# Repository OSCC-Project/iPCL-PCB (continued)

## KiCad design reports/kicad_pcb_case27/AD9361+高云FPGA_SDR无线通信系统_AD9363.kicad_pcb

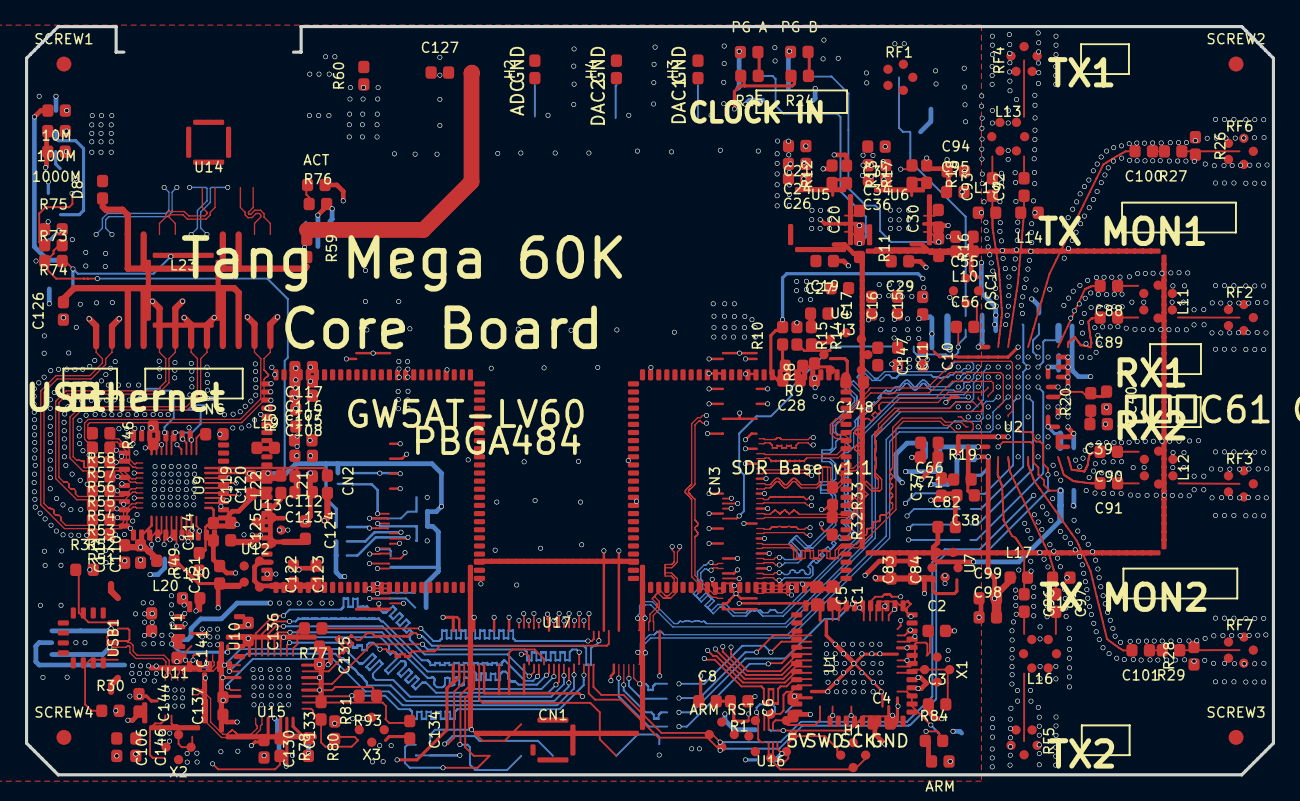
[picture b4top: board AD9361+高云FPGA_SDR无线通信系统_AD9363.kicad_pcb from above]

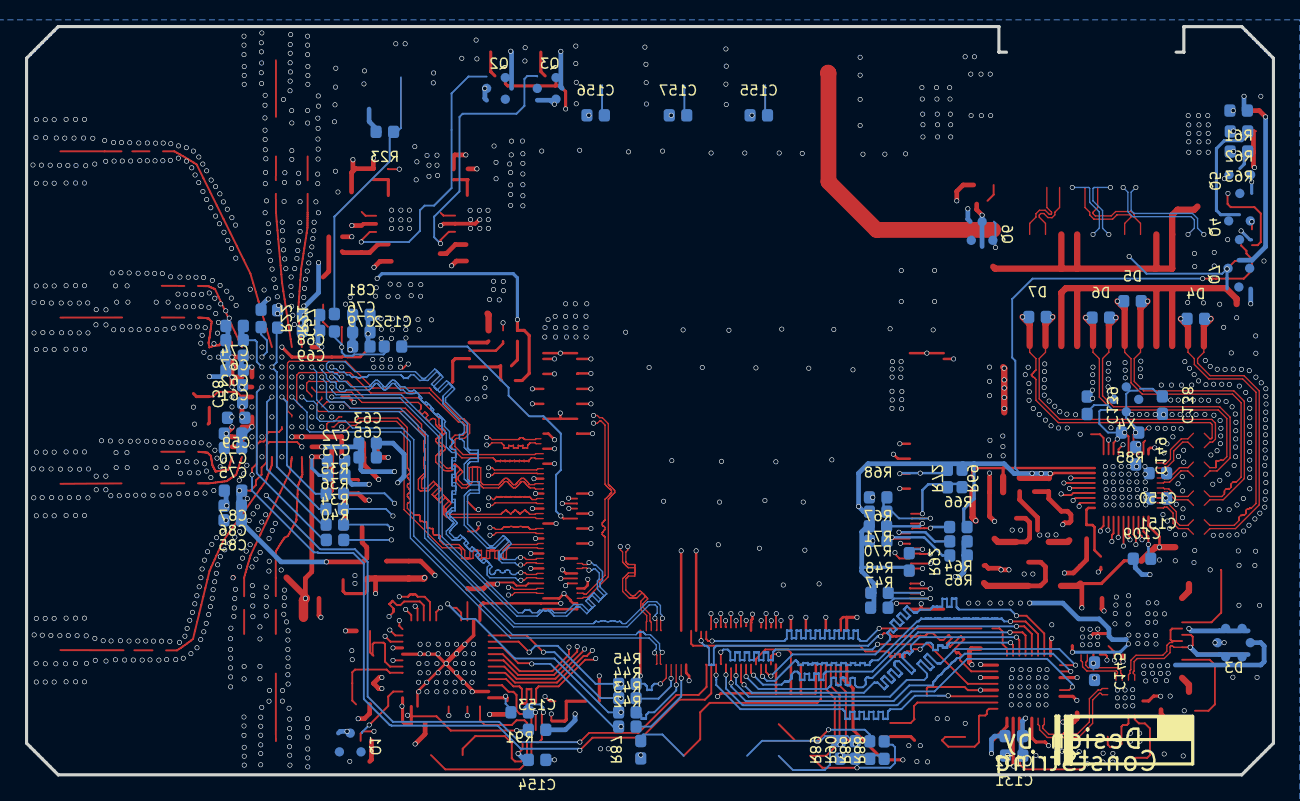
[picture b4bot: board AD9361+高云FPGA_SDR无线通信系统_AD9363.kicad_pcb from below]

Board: 4 copper layers, 100.0 x 60.0 mm, 274 parts (82 on the bottom side), 245 nets.

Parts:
10M, 100M, 1000M: 81ffb88415c44813ae88209955e7c78c
ACT: 81ffb88415c44813ae88209955e7c78c
ARM: 81ffb88415c44813ae88209955e7c78c
ARM RST: 7dd6720d68c446719365f3a60b06a3d4
C1, C2, C3, C4, C5, C6, C8, C20, C24, C26, C27, C28, C30, C34, C36, C37, C38, C39, C40, C55, C56, C57, C58, C59, C61, C62, C63, C65, C66, C67, C68, C69, C70, C71, C72, C73, C74, C75, C76, C79, C85, C86, C87, C88, C89, C90, C91, C92, C93, C95, C96, C97, C99, C100, C101, C107, C108, C109, C110, C111, C112, C113, C114, C115, C116, C117, C119, C120, C126, C130, C131, C133, C134, C135, C136, C137, C138, C139, C140, C141, C144, C145, C146, C147, C148, C149, C150, C151, C152, C153, C154, C155, C156, C157: 2218026411c24ad7aa8c7eefc9fb0747
C10, C11, C15, C16, C17: bd62313503d94485b107ad99fc121a58
C19, C21, C29, C31, C81, C82, C83, C84, C94, C98, C106, C121, C122, C123, C124, C125, C132: b6dbb5ff8ac44442903843d0a49ba1b4
C127: 1f480a04812e476d85878241a76d6dab
CN1: 7fd91c8eb86f4ef493fcae420cc5a236
CN2, CN3: b10a9c17a09f40588c51376b90a8528a
D3: 31aeffc65a7040bea0c61d6139a11c18
D4, D5, D6, D7: b31a530e17ae47c5b04672837fb6799c
D8: c10007abe38c47a7b87ab16ff611ce54
F1: e1e246e4058e4f2cb0164869e14091ad
H1: 507350d26ffb4301b926e73910155355
H2, H3, H4: 2a4ef173d7bb4178ba727836363a3722
L10, L20, L21, L22: 8e29569e39fd44aa8c43aaaf80cd9083
L11, L12, L13, L16: 63f67b374b2243b18a84cd74cbe2f3f3
L14, L15, L17, L18: 179f3791b8784cc680c437a3efdd4b04
L19: cbf6cd5da4ff4b4385b17ae7bcff98d5
L23: d78d442e09c0422188aa45615f3a3d0e
NC: 073582d7bdef4f49a1284c73eea18806
OSC1: 6182a2c878e549158f1d9c038c5ce7a3
PG A: 30f1d73fe7104a6986f78cf331c4975f
PG B: 30f1d73fe7104a6986f78cf331c4975f
Q1, Q2, Q3, Q4, Q5, Q6: f9aee2f635684ce29874ae31607c59e5
Q7: f5cc4a0a92d24ce5a40aa6a7c1fedc9f
R1, R8, R9, R10, R11, R12, R13, R14, R15, R16, R17, R18, R19, R20, R21, R22, R23, R24, R25, R26, R27, R28, R29, R30, R31, R32, R33, R34, R35, R36, R40, R42, R43, R44, R45, R46, R47, R48, R49, R50, R51, R52, R53, R54, R55, R56, R57, R58, R61, R62, R63, R64, R65, R66, R67, R68, R69, R70, R71, R72, R73, R74, R75, R76, R77, R78, R80, R81, R84, R85, R86, R87, R88, R89, R90, R91, R92, R93: 073582d7bdef4f49a1284c73eea18806
R59, R60: 98cf0348c8144cb19a93da813708cb62
RF1: aa04b55d95ab4d16b10c242528f5914c
RF2, RF3, RF4, RF5, RF6, RF7: f7525c14c0624ba49d44b90f489655c1
SCREW1: e584
SCREW2: e585
SCREW3: e587
SCREW4: e589
U1: d4d1bbb6b3024aa89e210277779a1524
U2: 44c17d15bf524a95900276da06795e90
U3: c65eff752ba2425191bd24655060057f
U4: b9df9a449868427a838a73cc143e1fe6
U5, U6: 34d530a420af4d6fbf68b1a8a67ad2c2
U7, U12, U13: fc24ab5a59e648c2b5c9dd79cfa5a276
U9: 6a1d45914ae84bee8d2c010ea94bd60d
U10: 1c7bc24088074f01866a2314a22fcef9
U11: 87c69e2cf3154d7c86d08ffd1fcbba79
U14: b9780a7aece7405fba878a3714394c2b
U15: 3f32b4c241834b3ba524ce5ae7f08632
U16: 68d9d0e5ebdd4a91b9118051fb54c8c4
U17: 091dc6707f3c4b86bc4edc7ea8aebfad
USB1: 090befb01a1c47f086e739b53b55ac0a
X1, X2, X3, X4: baa95a22880b4a62b1cd14ca4a928589

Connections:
1V3_A: C21.2, C24.2, C26.2, C58.2, C59.2, C61.2, C62.2, C63.2, C65.2, R12.2, U2.B9, U2.B10, U2.E2, U2.F2, U2.J3, U2.K3, U5.10, U5.11, U5.12, U5.13, U5.14
1V3_B: C31.2, C34.2, C36.2, C66.2, C67.2, C68.2, C69.2, C70.2, C71.2, C72.2, C73.2, C74.2, C75.2, C94.2, C95.2, C98.2, C99.2, L14.1, L15.1, L17.1, L18.1, R17.2, U2.A9, U2.A10, U2.D2, U2.D3, U2.E3, U2.F12, U2.K4, U2.M9, U2.M10, U6.10, U6.11, U6.12, U6.13, U6.14
1V8: C4.2, C5.2, C6.2, C15.2, C16.2, C17.2, C19.2, C28.2, C29.2, C76.2, C79.2, C81.2, C153.2, CN2.50, CN3.50, L10.2, R1.1, R10.2, R11.2, R16.2, R21.2, R91.1, U1.1, U1.9, U1.24, U1.36, U1.48, U2.H12, U4.2, U5.1, U5.2, U5.3, U5.4, U5.15, U5.16, U6.1, U6.2, U6.3, U6.4, U6.15, U6.16, U16.1, U17.26
3V3: C82.1, C85.2, C86.2, C87.2, C154.1, R86.2, R87.2, R88.2, R89.2, R90.2, U2.B8, U7.5, U16.8
5V: 100M.2, 1000M.2, ACT.2, C10.2, C11.2, C83.1, C84.2, C122.1, C123.2, C124.2, C141.1, C144.1, C147.2, CN2.1, CN2.2, CN2.3, CN2.4, CN2.5, CN2.6, F1.2, H1.1, Q7.2, R15.1, R24.2, R25.2, R78.2, R84.2, U3.2, U7.1, U7.3, U10.3, U10.9, U11.15, U12.1, U12.3, U13.1, U13.3
$2N1720: C37.2, R19.1
$2N3444: C39.2, R20.1
$2N3451: C40.1, R20.2, U2.G2, U2.G3
$2N3895: R22.1, U2.L4
$2N4930: C55.1, L10.1, OSC1.4
$2N4992: C56.2, OSC1.3
$2N5256: C57.1, R23.2, RF1.5
$3N848: R15.2, U3.6
$3N852: C27.2, U3.3, U4.1
$3N853: C27.1, R14.1
$3N854: R14.2, U3.5
$3N857: C28.1, R8.2, R9.1, U3.8
$3N1060: R9.2, R10.1
$3N1717: C20.2, U5.7
$3N1832: R12.1, R13.2, U5.9
$3N3032: C30.2, U6.7
$3N3034: R17.1, R18.2, U6.9
$3N6807: PG B.2, R24.1
$3N6848: PG A.2, R25.1
$3N15876: C148.2, U3.7
$3N21957: PG B.1, Q2.3
$3N22008: PG A.1, Q3.3
$4N680: C1.2, U1.22
$4N3637: ARM.2, R84.1
$4N6007: ARM.1, Q1.3
$4N6427: R91.2, U16.5
$5N375: R31.1, USB1.4
$5N379: R30.1, USB1.10
$5N1334: C145.2, U10.6
$5N1646: U11.2, X2.1
$5N1650: U11.1, X2.3
$5N1903: C106.1, C146.1, U11.16
$6N381: L11.3, RF2.5
$6N492: C88.1, L11.6
$6N497: C89.1, L11.4
$6N753: L12.3, RF3.5
$6N755: C90.1, L12.6
$6N758: C91.1, L12.4
$6N915: L13.3, RF4.5
$6N1077: C92.2, L13.4
$6N1083: C93.2, L13.6
$6N1770: C97.2, L16.6
$6N1788: C96.2, L16.4
$6N1797: L16.3, RF5.5
$6N2135: R26.2, R27.1, RF6.5
$6N2141: C100.1, R27.2
$6N2367: C101.1, R29.2
$6N2369: R28.2, R29.1, RF7.5
$7N989: L19.1, U9.30
$7N1109: NC.1, U9.31
$7N1265: R46.1, U9.39
$7N3719: D4.1, L23.1, R51.2
$7N3729: D4.2, L23.2, R52.2
$7N3751: D5.1, L23.5, R53.2
$7N3757: D5.2, L23.6, R54.2
$7N3761: D6.1, L23.7, R55.2
$7N3767: D6.2, L23.8, R56.2
$7N3774: D7.1, L23.11, R57.2
$7N3784: D7.2, L23.12, R58.2
$7N4429: C126.2, L23.3, L23.4, L23.9, L23.10
$7N4503: D8.1, L23.15, L23.16, L23.21, L23.22, R59.2
$7N4793: C127.2, R59.1
$7N8958: 10M.1, R61.1
$7N8975: 100M.1, R62.1
$7N8992: 1000M.1, R63.1
$7N9856: ACT.1, R76.1
$7N51860: Q4.3, R62.2
$7N51864: Q5.3, R63.2
$7N51869: Q6.3, R76.2
$7N52042: 10M.2, Q7.3
$8N749: R77.2, U15.1
$8N854: C130.1, U15.20, U15.23
$8N1159: R78.1, U15.22
$8N1371: R80.1, U15.24
$8N1466: C134.1, R81.1, U15.26, X3.1
$8N1479: C133.1, R81.2, U15.25, X3.3
ARM_COM_D0: U1.10, U17.62
ARM_COM_D1: U1.11, U17.61
ARM_COM_D2: U1.12, U17.60
ARM_COM_D3: U1.13, U17.57
ARM_COM_D4: U1.14, U17.56
ARM_COM_D5: U1.15, U17.55
ARM_COM_D6: U1.16, U17.54
ARM_COM_D7: U1.17, U17.53
ARM_COM_S0: U1.29, U17.63
ARM_COM_S1: U1.30, U17.64
ARM_COM_S2: U1.31, U17.65
ARM_COM_S3: U1.32, U17.66
ARM_COM_S4: U1.33, U17.67
ARM_LED: Q1.1, U1.2
ARM_NRST: ARM RST.2, C8.2, R1.2, U1.7
ARM_OSC_IN: C3.2, U1.5, X1.3
ARM_OSC_OUT: C2.1, U1.6, X1.1
ARM_SPI2_EN: R44.2, U1.26, U2.K6
ARM_SPI2_MISO: R45.2, U1.27, U2.L6
ARM_SPI2_MOSI: R42.2, U1.28, U2.J4
ARM_SPI2_SCK: R43.2, U1.21, U2.J5
ARM_SWCLK: U1.37, U16.2
ARM_SWCLK_3V3: H1.3, U16.6
ARM_SWDIO: U1.34, U16.3
ARM_SWDIO_3V3: H1.2, U16.7
ARM_UART_RX: U1.39, U10.4
ARM_UART_TX: U1.42, U10.5
AUX_ADC: C155.1, H2.1, U2.L5
AUX_DAC1: C156.1, H3.1, U2.B3
AUX_DAC2: C157.1, H4.1, U2.C3
BANK1_A13_IOT95A: CN3.26, U2.G9
BANK1_A14_IOT95B: CN3.27, R33.1, U2.H9
BANK1_A15_IOT99A: CN3.32, U2.F10
BANK1_A16_IOT99B: CN3.33, R32.1, U2.G10
BANK1_B13_IOT93B: CN3.24, U2.E9
BANK1_B15_IOT97A: CN3.29, U2.D10
BANK1_B16_IOT97B: CN3.30, U2.E11
BANK1_B17_IOT104A: CN3.38, U2.D11
BANK1_B18_IOT104B: CN3.39, U2.E12
BANK1_C13_IOT93A: CN3.23, U2.D8
BANK1_C14_IOT85A: CN3.20, U2.E7
BANK1_C15_IOT85B: CN3.21, U2.F8
BANK1_C17_IOT106B: CN3.36, U2.E10
BANK1_D14_IOT82A: C152.1, CN3.68
BANK1_D17_IOT106A: CN3.35, U2.D9
BANK1_E13_IOT78A: CN3.17, U2.D7
BANK1_E14_IOT78B: CN3.18, U2.E8
BANK1_F13_IOT80A: CN3.72, R35.1
BANK1_F14_IOT80B: CN3.71, R36.1
BANK1_F15: CN3.70, R34.1
BANK2_A18_IOT113A: CN3.41, U2.J12
BANK2_A19_IOT113B: CN3.42, U2.K11
BANK2_A20_IOT122B: CN3.45, U2.K10
BANK2_A21_IOT135B: CN3.48, U2.J7
BANK2_B20_IOT122A: CN3.44, U2.J11
BANK2_B21_IOT135A: CN3.47, U2.H8
BANK2_B22_IOT133B: U2.G7, U17.3
BANK2_C18_IOT115A: CN3.59, U2.G11
BANK2_C19_IOT115B: CN3.58, U2.H11
BANK2_C20_IOT131B: CN3.52, U2.K7
BANK2_C22_IOT133A: U2.G8, U17.4
BANK2_D19_IOT120B: CN3.55, R40.1
BANK2_D20_IOT131A: CN3.53, U2.J8
BANK2_D21_IOT138B: U2.J9, U17.80
BANK2_D22_IOT140B: U2.K9, U17.78
BANK2_E18_IOT117B: R45.1, U17.5
BANK2_E19_IOT120A: CN3.56, U2.J6
BANK2_E21_IOT138A: U2.K8, U17.79
BANK2_E22_IOT140A: U2.J10, U17.77
BANK2_F18_IOT117A: R44.1, U17.6
BANK2_G21_IOT144A: R42.1, U17.8
BANK2_G22_IOT144B: R43.1, U17.7
BANK5_H19_IOR41B: U15.31, U17.69
BANK5_H20_IOR43A: U15.2, U17.71
BANK5_H22_IOR45B: R93.2, U15.27, U17.15
BANK5_J19_IOR41A: R77.1, U17.68
BANK5_J20_IOR54A: U2.D6, U17.14
BANK5_J21_IOR54B: U2.E5, U17.13
BANK5_J22_IOR45A: U15.29, U17.16
BANK5_K21_IOR59A: U15.10, U17.18
BANK5_K22_IOR59B: U15.13, U17.17
BANK5_L19_IOR61A: U15.3, U17.20
BANK5_L20_IOR61B: U15.9, U17.19
BANK5_L21_IOR68B: U15.4, U17.21
BANK5_M21_IOR68A: U15.5, U17.22
BANK5_M22_IOR63B: U15.6, U17.24
BANK5_N22_IOR63A: U15.7, U17.25
BANK8_AA18_IOB77A: CN2.38, Q6.1
BANK8_AA19_IOB85A: CN2.42, U9.18
BANK8_AB18_IOB77B: C109.1, CN2.39, R92.2, U9.12
BANK8_AB20_IOB85B: CN2.43, U9.17
BANK8_AB21_IOB97A: CN2.46, U9.16
BANK8_AB22_IOB97B: CN2.47, U9.15
BANK8_U17_IOB75A: CN2.32, R69.1, R72.2, U9.25
BANK8_U18_IOB75B: CN2.33, R68.1, R71.2, U9.24
BANK8_V17_IOB79A: CN2.34, R67.1, R70.2, U9.23
BANK8_W17_IOB79B: CN2.35, R66.2, U9.22
BANK8_W19_IOB93A: CN2.40, U9.20
BANK8_W20_IOB93B: CN2.41, U9.19
BANK8_Y18_IOB87A: CN2.36, R64.1, U9.26
BANK8_Y19_IOB87B: CN2.37, R65.1, U9.27
BANK8_Y21_IOB99A: CN2.48, R48.1, U9.14
BANK8_Y22_IOB99B: CN2.49, R47.1, U9.13
BANK12_R13_JTAG_TDI: CN1.9, R87.1, U17.36
BANK12_T13_JTAG_TMS: CN1.5, R90.1, U17.39
BANK12_U13_JTAG_TDO: CN1.3, R89.1, U17.38
BANK12_V12_JTAG_TCK: CN1.1, R88.1, U17.37
DN: D3.1, D3.6, U11.11, USB1.5, USB1.7
DP: D3.3, D3.4, U11.12, USB1.6, USB1.8
ENABLE: R35.2, U2.G6
EN_AGC: R34.2, U2.G5
ETH0_MDI0_N: L23.14, U14.2
ETH0_MDI0_P: L23.13, U14.1
ETH0_MDI1_N: L23.18, U14.6
ETH0_MDI1_P: L23.17, U14.3
ETH0_MDI2_N: L23.20, U14.5
ETH0_MDI2_P: L23.19, U14.4
ETH0_MDI3_N: L23.24, U14.8
ETH0_MDI3_P: L23.23, U14.7
GND: ARM RST.3, C1.1, C2.2, C3.1, C4.1, C5.1, C6.1, C8.1, C10.1, C11.1, C15.1, C16.1, C17.1, C19.1, C20.1, C21.1, C24.1, C26.1, C29.1, C30.1, C31.1, C34.1, C36.1, C37.1, C38.2, C39.1, C40.2, C55.2, C58.1, C59.1, C61.1, C62.1, C63.1, C65.1, C66.1, C67.1, C68.1, C69.1, C70.1, C71.1, C72.1, C73.1, C74.1, C75.1, C76.1, C79.1, C81.1, C82.2, C83.2, C84.1, C85.1, C86.1, C87.1, C94.1, C95.1, C98.1, C99.1, C106.2, C107.2, C108.2, C109.2, C110.1, C111.1, C112.1, C113.1, C114.1, C115.1, C116.1, C117.1, C119.1, C120.1, C121.2, C122.2, C123.1, C124.1, C125.1, C126.1, C130.2, C131.1, C132.1, C133.2, C134.2, C135.1, C136.1, C137.1, C138.1, C139.2, C140.2, C141.2, C144.2, C145.1, C146.2, C147.1, C148.1, C149.1, C150.1, C151.1, C153.1, C154.2, C155.2, C156.2, C157.2, CN1.10, CN2.7, CN2.8, CN2.9, CN2.10, CN2.11, CN2.12, CN2.18, CN2.21, CN2.24, CN2.27, CN2.100, CN3.1, CN3.4, CN3.7, CN3.10, CN3.13, CN3.16, CN3.19, CN3.22, CN3.25, CN3.28, CN3.31, CN3.34, CN3.37, CN3.40, CN3.43, CN3.46, CN3.49, CN3.51, CN3.54, CN3.57, CN3.60, CN3.63, CN3.66, CN3.69, CN3.73, CN3.85, CN3.88, CN3.91, CN3.94, CN3.97, CN3.100, D3.2, H1.4, H2.2, H3.2, H4.2, L11.1, L11.2, L11.5, L12.1, L12.2, L12.5, L13.1, L13.2, L13.5, L16.1, L16.2, L16.5, NC.2, OSC1.2, Q1.2, Q2.2, Q3.2, Q4.2, Q5.2, Q6.2, R8.1, R13.1, R18.1, R22.2, R23.1, R26.1, R28.1, R30.2, R31.2, R32.2, R33.2, R46.2, R60.1, R61.2, R64.2, R65.2, R67.2, R68.2, R69.2, R75.2, R80.2, RF1.1, RF1.2, RF1.3, RF1.4, RF2.1, RF2.2, RF2.3, RF2.4, RF3.1, RF3.2, RF3.3, RF3.4, RF4.1, RF4.2, RF4.3, RF4.4, RF5.1, RF5.2, RF5.3, RF5.4, RF6.1, RF6.2, RF6.3, RF6.4, RF7.1, RF7.2, RF7.3, RF7.4, U1.8, U1.23, U1.35, U1.47, U1.49, U2.A4, U2.A6, U2.A12, U2.B1, U2.B2, U2.B12, U2.C1, U2.C2, U2.C4, U2.C7, U2.C8, U2.C9, U2.C10, U2.C11, U2.C12, U2.D1, U2.D12, U2.E1, U2.F1, U2.F3, U2.F7, U2.F9, U2.F11, U2.G1, U2.G12, U2.H1, U2.H2, U2.H3, U2.H5, U2.H6, U2.H7, U2.H10, U2.J1, U2.J2, U2.K1, U2.K2, U2.K12, U2.L1, U2.L2, U2.L3, U2.L7, U2.L8, U2.L9, U2.L10, U2.L11, U2.L12, U2.M4, U2.M6, U3.1, U3.4, U5.6, U5.17, U6.6, U6.17, U7.2, U9.41, U10.2, U10.17, U11.17, U12.2, U13.2, U15.33, U16.4, U17.9, U17.23, U17.27, U17.30, U17.32, U17.35, U17.40, U17.41, U17.44, U17.48, U17.51, U17.59, U17.70, U17.73, USB1.1, USB1.12, USB1.13, USB1.14, X1.2, X1.4, X2.2, X2.4, X3.2, X3.4, X4.2, X4.4
GNDS: C127.1, D8.2, R60.2, U14.9, U14.10
JTAG_VREF: CN1.4, R86.1
PG_1V3_A: Q3.1, R11.1, U5.5
PG_1V3_B: Q2.1, R16.1, U6.5
PHY0_1V8: C125.2, C135.2, C136.2, C137.2, C140.1, L22.1, R93.1, U10.1, U13.5, U15.8, U15.11, U15.14, U15.28, U15.30, U15.32
PHY0_3V3: C121.1, C131.2, C132.2, L20.1, L21.1, U12.5, U15.21
PHY0_AVDD_1V0: C115.2, C116.2, C117.2, C149.2, C150.2, C151.2, R50.2, U9.3, U9.8, U9.38
PHY0_AVDD_3V3: C110.2, C111.2, L20.2, U9.11, U9.40
PHY0_DVDD_1V0: C114.2, R49.2, U9.21
PHY0_DVDD_3V3: C112.2, C113.2, L21.2, U9.29
PHY0_LED0/CFG_EXT: Q7.1, R73.2, U9.32
PHY0_LED1/CFG_LDO0: Q4.1, R75.1, U9.33
PHY0_LED2/CFG_LDO1: Q5.1, R74.2, U9.34
PHY0_MDI0_N: R57.1, U9.2
PHY0_MDI0_P: R58.1, U9.1
PHY0_MDI1_N: R55.1, U9.5
PHY0_MDI1_P: R56.1, U9.4
PHY0_MDI2_N: R53.1, U9.7
PHY0_MDI2_P: R54.1, U9.6
PHY0_MDI3_N: R51.1, U9.10
PHY0_MDI3_P: R52.1, U9.9
PHY0_REG_1V0: C107.1, C108.1, L19.2, R49.1, R50.1
PHY0_VIO: C119.2, C120.2, L22.2, R47.2, R48.2, R66.1, R70.1, R71.1, R72.1, R73.1, R74.1, R92.1, U9.28
PHY0_XTAL_IN: C139.1, R85.1, U9.36, X4.1
PHY0_XTAL_OUT: C138.2, R85.2, U9.37, X4.3
RESETB: R21.1, R36.2, U2.K5
RX1A_N: C88.2, U2.M2
RX1A_P: C89.2, U2.M1
RX2A_N: C90.2, U2.A1
RX2A_P: C91.2, U2.A2
TX1A_N: C93.1, L15.2, U2.M8
TX1A_P: C92.1, L14.2, U2.M7
TX2A_N: C97.1, L18.2, U2.A7
TX2A_P: C96.1, L17.2, U2.A8
TXNRX: R40.2, U2.H4
TX_MON1: C100.2, U2.M5
TX_MON2: C101.2, U2.A5
TX_VCO_1V1: C38.1, R19.2, U2.A11, U2.B11
USART_DN: U10.8, U11.9
USART_DP: U10.7, U11.10
USB_DN: U11.7, U15.19
USB_DP: U11.8, U15.18
VBUS: D3.5, F1.1, USB1.2, USB1.11
XTALN: C56.1, C57.2, C152.2, U2.M12

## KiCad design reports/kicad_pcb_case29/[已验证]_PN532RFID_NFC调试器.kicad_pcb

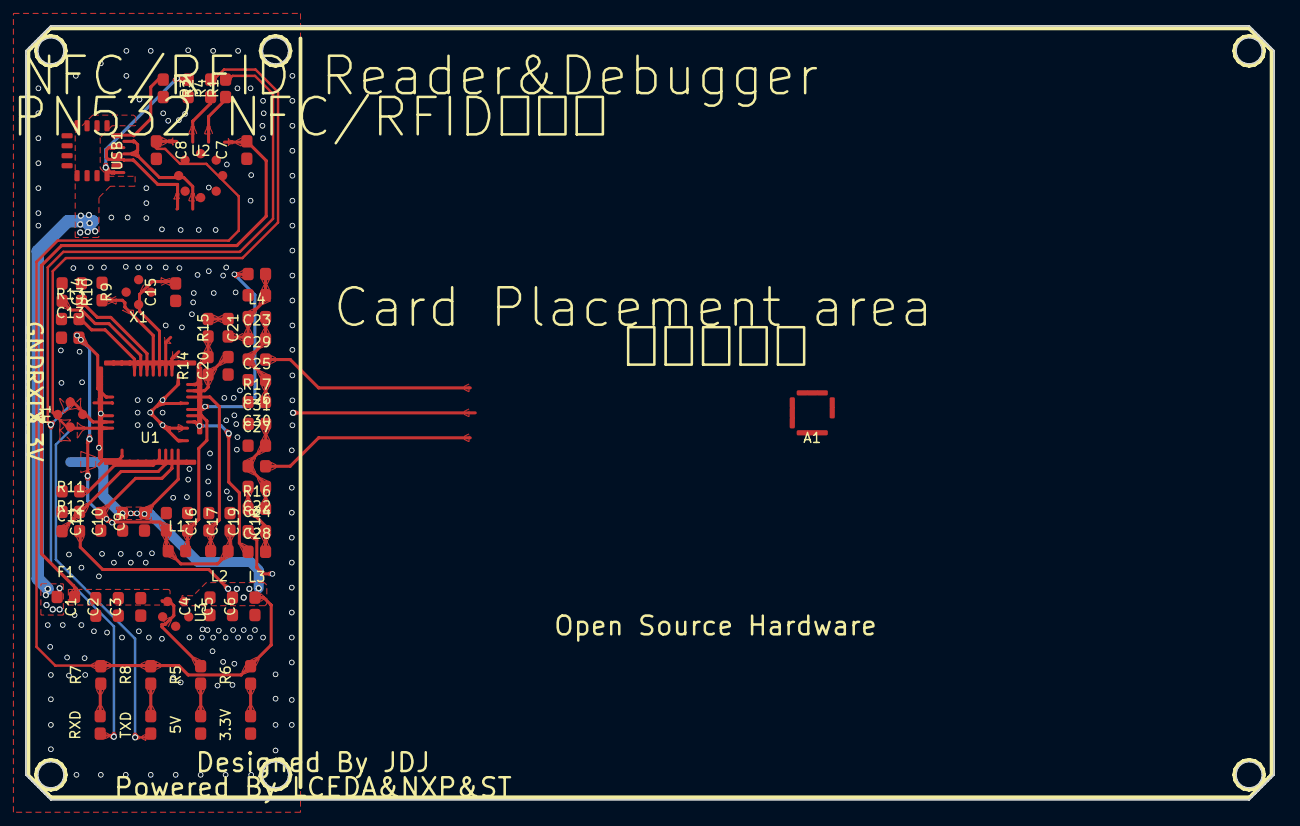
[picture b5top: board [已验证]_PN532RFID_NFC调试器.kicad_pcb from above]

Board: 4 copper layers, 100.0 x 62.0 mm, 64 parts (0 on the bottom side), 37 nets.

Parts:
3.3V: e18
5V: e17
A1: 7a9f0954cb3d4d10918b51f45fdb83fd
C1, C2, C3, C4, C5, C6, C7, C8, C9, C10, C11, C12, C13, C14, C15, C16, C17, C18, C19, C20, C21, C22, C23, C24, C25, C26, C27, C28, C29, C30, C31: 8f7a3719ddcd4fd8b3f45622f7cba8cd
F1: f3e1269709494694a1d8bce25b8ee1e8
H1: 03f4122eac2b40b49db6fc08b820e069
L1, L2, L3, L4: 720e450fbc4b486db1884a2c420b49c0
R1, R2, R5, R6, R7, R8, R9, R10, R11, R12, R14, R15, R16, R17: 0198c72b9ff6426ea0ee71ada792c43b
R3, R4, R13: 1064866dc1bf4bbd83bcacf9a79b5dbc
RXD: e19
TXD: e20
U1: 15638c3e09104a739cadb23dd1c3f9aa
U2: b1a0bcdb47574bcab0503576b89ba266
U3: 60e3120b69094052863bedef18c525dc
USB1: c94ffee73b93482cada48766b6ee1610
X1: 0f1cdad729404e7a8c291a360b05ecb5

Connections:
3.3V: C4.2, C5.2, C6.2, C8.1, C9.2, C10.2, H1.1, R6.2, R7.2, R8.2, R12.2, U1.40, U2.8, U3.5
5V: C1.2, C2.2, C3.2, C7.2, F1.2, R5.2, U2.5, U3.1, U3.3
532_RXD: H1.3, R4.2, RXD.1, U1.27
532_TXD: H1.2, R3.2, TXD.1, U1.28
$1N415: R1.1, USB1.B5
$1N465: R2.1, USB1.A5
$1N1931: R7.1, RXD.2
$1N1933: R8.1, TXD.2
$1N1935: 3.3V.2, R6.1
$1N1938: 5V.2, R5.1
$1N2593: C11.1, U1.37
$1N2815: R13.2, U1.18
$1N3520: C21.1, R15.2
$1N3576: L4.2, U1.6
$1N3579: L3.2, U1.4
$1N3784: C22.2, C24.2, C28.2, L3.1
$1N4004: C24.1, C26.2, C28.1, C30.2, R16.2
$1N4012: C25.1, C27.1, C29.1, C31.1, R17.2
ANT_TX1: A1.1, R16.1
ANT_TX2: A1.3, R17.1
AVDD: C19.2, L2.2, U1.8
CH340_RXD: R3.1, U2.7
CH340_TXD: R4.1, U2.6
GND: 3.3V.1, 5V.1, A1.2, C1.1, C2.1, C3.1, C4.1, C5.1, C6.1, C7.1, C8.2, C9.1, C10.1, C11.2, C12.1, C13.1, C14.2, C15.1, C16.1, C17.1, C18.1, C19.1, C20.1, C22.1, C23.2, C26.1, C27.2, C30.1, C31.2, H1.4, R1.2, R2.2, R9.1, R10.1, R11.1, R13.1, U1.1, U1.3, U1.7, U1.11, U1.41, U2.3, U3.2, USB1.13, USB1.14, USB1.15, USB1.16, USB1.A1B12, USB1.B1A12, X1.2, X1.4
OSCIN: C15.2, U1.14, X1.1
OSCOUT: C14.1, U1.15, X1.3
RES&OFF: R11.2, R12.1, U1.38
RX: C21.2, R14.2, U1.10
RXIN: C23.1, C25.2, C29.2, L4.1, R15.1
SET0: R9.2, U1.16
SET1: R10.2, U1.17
TVDD: C17.2, L1.2, U1.5
USB_N: U2.2, USB1.A7, USB1.B7
USB_P: U2.1, USB1.A6, USB1.B6
VBUS: F1.1, USB1.A4B9, USB1.B4A9
VMID: C20.2, R14.1, U1.9
VREF: C12.2, C13.2, C16.2, C18.2, L1.1, L2.1, U1.23, U1.39

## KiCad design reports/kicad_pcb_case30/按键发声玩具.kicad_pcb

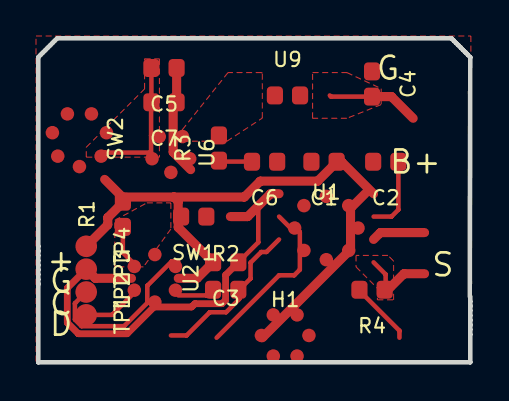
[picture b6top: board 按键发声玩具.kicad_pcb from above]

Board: 4 copper layers, 24.0 x 18.0 mm, 22 parts (0 on the bottom side), 15 nets.

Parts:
C1, C2, C3, C4, C5, C6, C7: bb17d5219181498b9e1395dbbf8b2fe0
H1: 36dfb2ea8d0e4e4f941cdac11c2fdbcb
R1, R2, R3, R4: 6658a532062f413bbac78fd6cbacbec5
SW1: 0139965c3fc24029a6435b55c53d32a5
SW2: 4f7abb5580174329a4a8b603a65d0e32
TP1, TP2, TP3, TP4: 59b65f4f99964ad8baf1fa180364e617
U1: 18bc969258c74e7298cb5068ceb95bdf
U2: 1f7687c352a74bcf9a3411407622aafa
U6: df62239e231b484093deec575f9a38e3
U9: e988ea007c7f4b938b03e561bd5e10d0

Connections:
$1N3367: R2.1, U2.4
$1N6451: C6.2, R3.1
$1N6655: H1.6, R4.2
BAT+: C4.2, U9.2
CLK: TP2.1, U2.6
DAT: TP1.1, U2.3
DATA/TX: H1.1, R2.2, U1.3
GND: C1.2, C2.2, C3.1, C4.1, C5.1, C6.1, C7.1, H1.4, H1.5, SW1.1, TP3.1, U1.1, U2.2, U6.4
RX: H1.2, U1.2
SPK1: R4.1, U1.5
SW: R3.2, U6.5, U9.1
SW1: R1.1, SW1.2, U2.1
VCC: C1.1, C3.2, H1.3, R1.2, SW2.3, TP4.1, U1.8, U2.5
VOUT: C5.2, C7.2, SW2.2, U6.1, U6.2
VREF: C2.1, U1.7

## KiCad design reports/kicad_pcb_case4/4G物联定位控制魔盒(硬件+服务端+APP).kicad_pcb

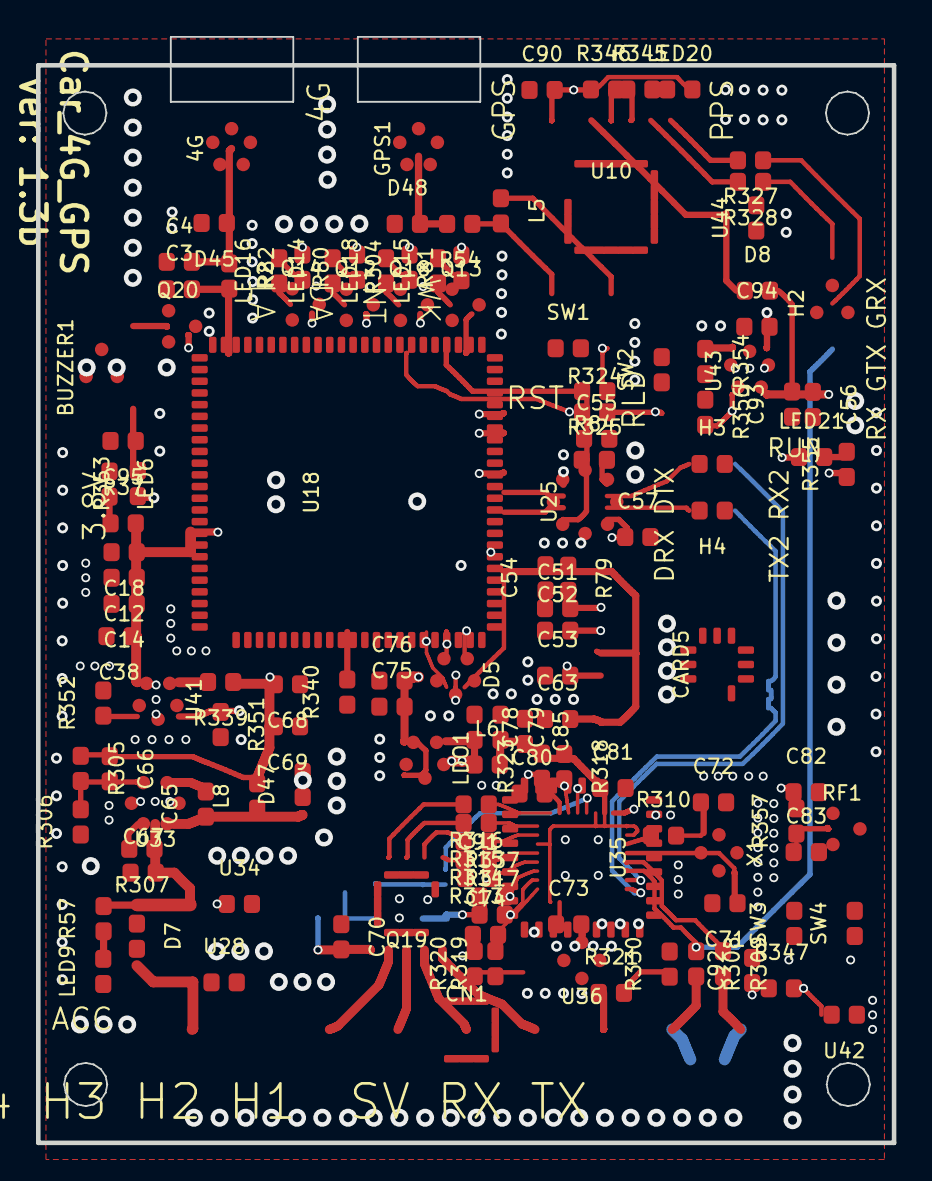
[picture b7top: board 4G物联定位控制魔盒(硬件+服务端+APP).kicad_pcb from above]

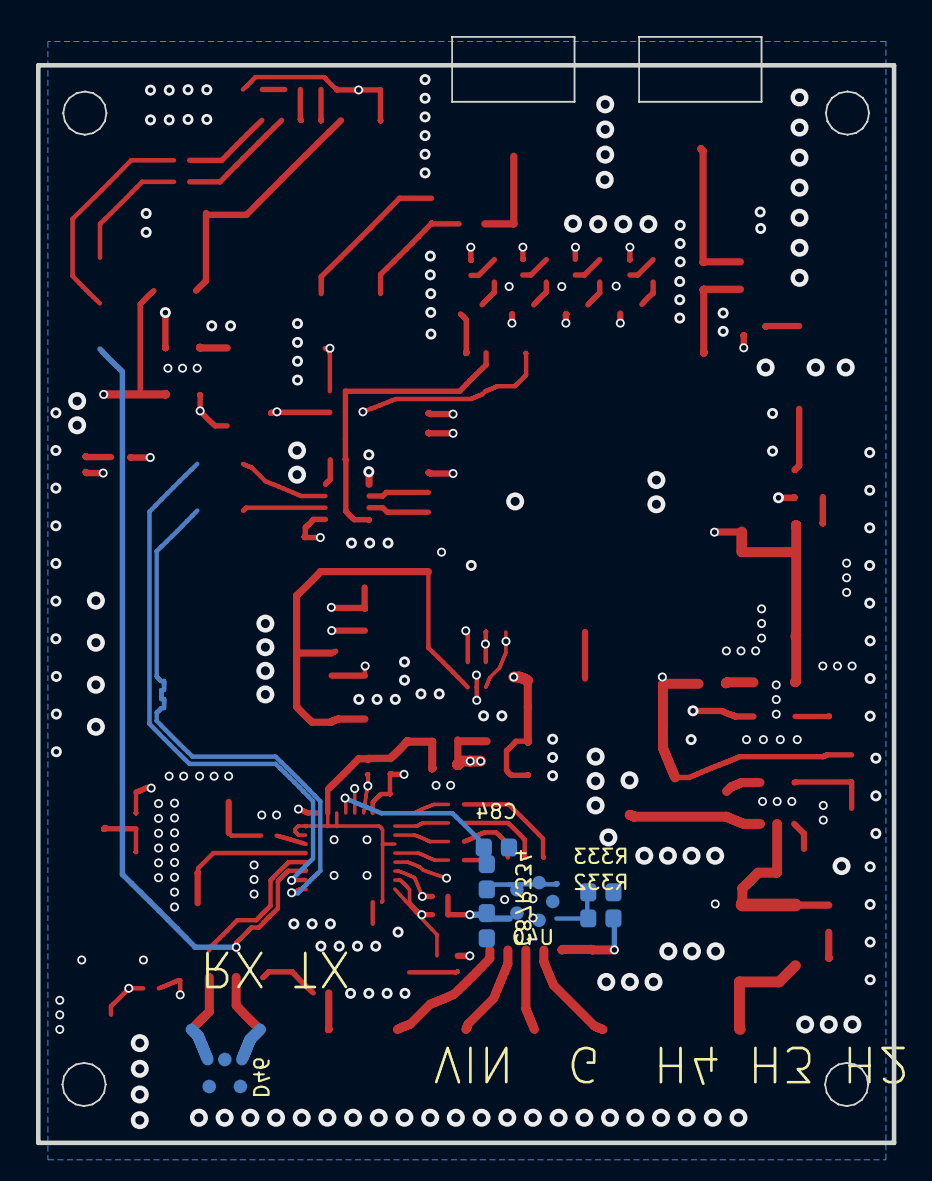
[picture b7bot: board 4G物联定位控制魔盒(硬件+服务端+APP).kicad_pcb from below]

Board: 4 copper layers, 47.5 x 61.4 mm, 140 parts (7 on the bottom side), 95 nets.

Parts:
4G: 339b1e6e8fa648a1980ca63f91b066e5_e38
BUZZER1: 339b1e6e8fa648a1980ca63f91b066e5_e32
C3: 339b1e6e8fa648a1980ca63f91b066e5_e25
C4: 339b1e6e8fa648a1980ca63f91b066e5_e27
C12: 339b1e6e8fa648a1980ca63f91b066e5_e17495
C14: 339b1e6e8fa648a1980ca63f91b066e5_e17496
C18: 339b1e6e8fa648a1980ca63f91b066e5_e17497
C38: e750a4c8b82b4072bef5e39c81e1ac36
C51: 339b1e6e8fa648a1980ca63f91b066e5_e3400
C52: 339b1e6e8fa648a1980ca63f91b066e5_e3401
C53: 339b1e6e8fa648a1980ca63f91b066e5_e3402
C54: 339b1e6e8fa648a1980ca63f91b066e5_e3403
C55: 339b1e6e8fa648a1980ca63f91b066e5_e10960
C56: 339b1e6e8fa648a1980ca63f91b066e5_e10961
C57: 339b1e6e8fa648a1980ca63f91b066e5_e10962
C63: 339b1e6e8fa648a1980ca63f91b066e5_e7494
C65: 339b1e6e8fa648a1980ca63f91b066e5_e8
C66: 339b1e6e8fa648a1980ca63f91b066e5_e12
C67: 339b1e6e8fa648a1980ca63f91b066e5_e876
C68: 339b1e6e8fa648a1980ca63f91b066e5_e2806
C69: 339b1e6e8fa648a1980ca63f91b066e5_e2807
C70: 339b1e6e8fa648a1980ca63f91b066e5_e9183
C71: 339b1e6e8fa648a1980ca63f91b066e5_e16717
C72: 339b1e6e8fa648a1980ca63f91b066e5_e16718
C73: 339b1e6e8fa648a1980ca63f91b066e5_e1355
C74: 339b1e6e8fa648a1980ca63f91b066e5_e1907
C75: 339b1e6e8fa648a1980ca63f91b066e5_e19874
C76: 339b1e6e8fa648a1980ca63f91b066e5_e19875
C78: 339b1e6e8fa648a1980ca63f91b066e5_e20200
C79: 339b1e6e8fa648a1980ca63f91b066e5_e20201
C80: 339b1e6e8fa648a1980ca63f91b066e5_e20422
C81: 339b1e6e8fa648a1980ca63f91b066e5_e24678
C82: 339b1e6e8fa648a1980ca63f91b066e5_e15832
C83: 339b1e6e8fa648a1980ca63f91b066e5_e15833
C84: 339b1e6e8fa648a1980ca63f91b066e5_e16918
C85: 339b1e6e8fa648a1980ca63f91b066e5_e19084
C87: 339b1e6e8fa648a1980ca63f91b066e5_e916
C90: 339b1e6e8fa648a1980ca63f91b066e5_e1018
C91: 339b1e6e8fa648a1980ca63f91b066e5_e4428
C92: 339b1e6e8fa648a1980ca63f91b066e5_e4429
C93: 339b1e6e8fa648a1980ca63f91b066e5_e6555
C94: 339b1e6e8fa648a1980ca63f91b066e5_e6556
C95: 339b1e6e8fa648a1980ca63f91b066e5_e39
CARD5: 339b1e6e8fa648a1980ca63f91b066e5_e491
CN1: faddb0dc836e4a918d7231af369a1492
D5: 339b1e6e8fa648a1980ca63f91b066e5_e7844
D7: 339b1e6e8fa648a1980ca63f91b066e5_e7
D8: 339b1e6e8fa648a1980ca63f91b066e5_e6661
D45: 339b1e6e8fa648a1980ca63f91b066e5_e13789
D46: 339b1e6e8fa648a1980ca63f91b066e5_e18401
D47: 339b1e6e8fa648a1980ca63f91b066e5_e9
D48: 339b1e6e8fa648a1980ca63f91b066e5_e1
GPS1: 339b1e6e8fa648a1980ca63f91b066e5_e2809
H2: 649f23d0a9e84efea2045ae1a5beec51
H3, H4: 3fd0e9248a124bdf82e83ce74b02eb12
L5: 339b1e6e8fa648a1980ca63f91b066e5_e6653
L6: 339b1e6e8fa648a1980ca63f91b066e5_e20237
L8: 339b1e6e8fa648a1980ca63f91b066e5_e15374
LDO1: 339b1e6e8fa648a1980ca63f91b066e5_e10435
LED6: 339b1e6e8fa648a1980ca63f91b066e5_e1113
LED9: 339b1e6e8fa648a1980ca63f91b066e5_e2
LED14: 339b1e6e8fa648a1980ca63f91b066e5_e5095
LED15: 339b1e6e8fa648a1980ca63f91b066e5_e5080
LED16: 339b1e6e8fa648a1980ca63f91b066e5_e5140
LED18: 339b1e6e8fa648a1980ca63f91b066e5_e5096
LED20: 339b1e6e8fa648a1980ca63f91b066e5_e1020
LED21: f5d6b86707ae4cf5be2b516e339955cc
Q12: 339b1e6e8fa648a1980ca63f91b066e5_e5081
Q13: 339b1e6e8fa648a1980ca63f91b066e5_e5119
Q14: 339b1e6e8fa648a1980ca63f91b066e5_e5146
Q18: 339b1e6e8fa648a1980ca63f91b066e5_e5109
Q19: 5222251922f44339af2e38a5e1c4eb8c
Q20: 339b1e6e8fa648a1980ca63f91b066e5_e34
R2: 339b1e6e8fa648a1980ca63f91b066e5_e29
R37: 339b1e6e8fa648a1980ca63f91b066e5_e1115
R54: 339b1e6e8fa648a1980ca63f91b066e5_e6665
R57: 339b1e6e8fa648a1980ca63f91b066e5_e31
R79: 339b1e6e8fa648a1980ca63f91b066e5_e8346
R80: 339b1e6e8fa648a1980ca63f91b066e5_e5100
R81: 339b1e6e8fa648a1980ca63f91b066e5_e5127
R82: 339b1e6e8fa648a1980ca63f91b066e5_e5099
R84: 339b1e6e8fa648a1980ca63f91b066e5_e10748
R304: 339b1e6e8fa648a1980ca63f91b066e5_e5154
R305: 339b1e6e8fa648a1980ca63f91b066e5_e10
R306: 339b1e6e8fa648a1980ca63f91b066e5_e11
R307: 339b1e6e8fa648a1980ca63f91b066e5_e13
R308: 339b1e6e8fa648a1980ca63f91b066e5_e14995
R309: 339b1e6e8fa648a1980ca63f91b066e5_e14996
R310: 339b1e6e8fa648a1980ca63f91b066e5_e15997
R313: 339b1e6e8fa648a1980ca63f91b066e5_e100
R314: 339b1e6e8fa648a1980ca63f91b066e5_e101
R315: 339b1e6e8fa648a1980ca63f91b066e5_e102
R316: 339b1e6e8fa648a1980ca63f91b066e5_e103
R317: 339b1e6e8fa648a1980ca63f91b066e5_e104
R318: 339b1e6e8fa648a1980ca63f91b066e5_e105
R319: 339b1e6e8fa648a1980ca63f91b066e5_e1905
R320: 339b1e6e8fa648a1980ca63f91b066e5_e1906
R321: 339b1e6e8fa648a1980ca63f91b066e5_e3436
R323: 339b1e6e8fa648a1980ca63f91b066e5_e20423
R324: 339b1e6e8fa648a1980ca63f91b066e5_e42943
R325: 339b1e6e8fa648a1980ca63f91b066e5_e43660
R327: 339b1e6e8fa648a1980ca63f91b066e5_e1124
R328: 339b1e6e8fa648a1980ca63f91b066e5_e1125
R330: 339b1e6e8fa648a1980ca63f91b066e5_e13627
R332: 339b1e6e8fa648a1980ca63f91b066e5_e16577
R333: 339b1e6e8fa648a1980ca63f91b066e5_e16578
R334: 339b1e6e8fa648a1980ca63f91b066e5_e18261
R337: 339b1e6e8fa648a1980ca63f91b066e5_e5
R339: 339b1e6e8fa648a1980ca63f91b066e5_e414
R340: 339b1e6e8fa648a1980ca63f91b066e5_e1676
R345: 339b1e6e8fa648a1980ca63f91b066e5_e1019
R346: 339b1e6e8fa648a1980ca63f91b066e5_e1021
R347: 339b1e6e8fa648a1980ca63f91b066e5_e3969
R351: 339b1e6e8fa648a1980ca63f91b066e5_e21433
R352: 339b1e6e8fa648a1980ca63f91b066e5_e21439
R353: 339b1e6e8fa648a1980ca63f91b066e5_e196
R354: 339b1e6e8fa648a1980ca63f91b066e5_e30
R355: 339b1e6e8fa648a1980ca63f91b066e5_e6858
R356: 339b1e6e8fa648a1980ca63f91b066e5_e12592
R357: 339b1e6e8fa648a1980ca63f91b066e5_e526
RF1: 339b1e6e8fa648a1980ca63f91b066e5_e515
SW1: 339b1e6e8fa648a1980ca63f91b066e5_e1088
SW2: 339b1e6e8fa648a1980ca63f91b066e5_e1089
SW3: 339b1e6e8fa648a1980ca63f91b066e5_e26186
SW4: 339b1e6e8fa648a1980ca63f91b066e5_e425
U10: 01dd7c36c8bf47dabde00ff9bb099edb
U18: 339b1e6e8fa648a1980ca63f91b066e5_e4
U25: 5d40c9c65c274b96a15051a764caa424
U28: 339b1e6e8fa648a1980ca63f91b066e5_e3588
U33: 339b1e6e8fa648a1980ca63f91b066e5_e3
U34: 339b1e6e8fa648a1980ca63f91b066e5_e875
U35: 339b1e6e8fa648a1980ca63f91b066e5_e11819
U36: d30c9ffffcdf4527a1d2ac3f679398fa
U40: 339b1e6e8fa648a1980ca63f91b066e5_e16576
U41: 339b1e6e8fa648a1980ca63f91b066e5_e14
U42: 339b1e6e8fa648a1980ca63f91b066e5_e3354
U43: 339b1e6e8fa648a1980ca63f91b066e5_e6
U44: 339b1e6e8fa648a1980ca63f91b066e5_e178
X1: 339b1e6e8fa648a1980ca63f91b066e5_e14994

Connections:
1.8V: C55.1, R84.1, R324.1, R325.2, U18.24, U25.8
3.3V: C56.1, C57.1, C78.2, C87.2, C92.1, C93.2, D8.2, L6.1, LDO1.5, R317.1, R320.2, R337.1, R347.1, R353.1, R355.1, U25.1, U40.5, U43.5
3.8V: C12.1, C14.1, C18.1, C38.1, R37.2, R80.2, R81.2, R82.2, R304.2, U18.42, U18.43, U41.1
3P3: C79.2, C81.1, C85.2, L6.2, R318.1, R323.2, U35.2, U35.3, U35.11, U35.17, U35.31, U35.32
4G_RX: H4.2, U25.2
4G_TX: H3.1, U25.3
$1N20618: LED6.2, R37.1
$1N54167: LED16.1, R82.1
$1N61856: 4G.5, C4.2, D45.1, R2.1
$1N69684: U18.17, U25.7
$1N69688: U18.18, U25.6
$1N107224: LED9.2, R57.1
$1N114200: R84.2, U25.4
$1N114847: LED14.2, Q12.3
$1N114849: LED14.1, R80.1
$1N114891: LED15.2, Q13.3
$1N114893: LED15.1, R81.1
$1N114935: LED16.2, Q14.3
$1N115529: CN1.1, D7.2, U28.1
$1N118782: LED18.1, R304.1
$1N118786: LED18.2, Q18.3
$1N126364: C65.1, D47.1, L8.2, U33.6
$1N126416: C65.2, U33.1
$1N126697: C66.2, R305.2, R306.2, U33.3
$1N126733: R307.2, U33.4
$1N127295: CN1.9, D46.2, R309.2
$1N127302: CN1.8, D46.1, R308.2
$1N133266: R334.1, U40.3, U40.4
$1N133305: R332.2, R333.2, U40.1
$1N135408: R340.2, U18.7
$1N140237: R352.1, U41.3
$1N141843: BUZZER1.2, Q20.3
$1N141927: BUZZER1.1, C95.1, R353.2
$2N1096: R310.1, U35.30
$2N1961: Q19.1, R313.2
$2N1993: Q19.2, R314.2
$2N2025: Q19.3, R315.2
$2N2081: Q19.4, R316.2
$2N2371: C73.1, U35.18
$2N2547: R319.1, R320.1, U36.4
$2N2631: C74.2, R319.2, U35.16
$2N2711: R321.2, R330.1, U36.1
$2N3401: L5.2, R54.1, U10.11
$2N3402: D48.2, GPS1.5, R54.2
$2N3403: L5.1, U10.14
$2N3406: R327.2, U10.2
$2N3407: R328.2, U10.3
$2N3413: D8.1, U10.6, U44.2
$2N3414: R346.2, U10.5
$2N8837: C82.1, R357.2, U35.1
$2N19485: LED20.1, R345.2
$2N21424: R354.1, U43.3
$2N21482: H2.2, R327.1
$2N21844: LED21.2, R355.2
$2N23624: C83.1, R357.1, RF1.1
ADC0: C84.2, R334.2, U35.4
ANT: C3.2, R2.2, U18.35
DATA: Q12.1, U18.21
DOW: R317.2, SW3.1, U35.15
EN: C80.2, R323.1, SW4.1, U35.7
FB: C66.1, C68.2, C69.2, C75.2, C76.2, L8.1, LDO1.1, LDO1.3, R305.1, R339.1
G3.3: C90.2, C94.2, LED20.2, R346.1, U10.8, U43.1
GA: CN1.7, R321.1
GEN: R356.2, U35.5, U43.4
GND: 4G.1, 4G.2, 4G.3, 4G.4, C3.1, C4.1, C12.2, C14.2, C18.2, C38.2, C51.1, C52.1, C53.1, C54.1, C55.2, C56.2, C57.2, C63.1, C67.1, C68.1, C69.1, C70.1, C71.2, C72.2, C73.2, C74.1, C75.1, C76.1, C78.1, C79.1, C80.1, C81.2, C82.2, C83.2, C84.1, C85.1, C87.1, C90.1, C91.1, C92.2, C93.1, C94.1, C95.2, CARD5.5, CARD5.8, CARD5.9, CARD5.10, CARD5.11, CN1.2, D5.2, D45.2, D46.3, D47.2, D48.1, GPS1.1, GPS1.2, GPS1.3, GPS1.4, LDO1.2, LED6.1, LED9.1, Q12.2, Q13.2, Q14.2, Q18.2, Q19.5, Q20.2, R306.1, R330.2, R333.1, R340.1, R351.2, R352.2, R354.2, R356.1, RF1.2, RF1.3, SW1.1, SW2.2, SW3.2, SW4.2, U10.1, U10.10, U10.12, U18.1, U18.10, U18.27, U18.34, U18.36, U18.37, U18.40, U18.41, U18.45, U18.46, U18.47, U18.48, U18.70, U18.71, U18.72, U18.73, U18.88, U18.89, U18.90, U18.91, U18.92, U18.93, U18.94, U25.5, U28.2, U33.2, U34.2, U35.33, U36.2, U36.3, U40.2, U41.2, U42.1, U43.2, U44.1, X1.2, X1.4
GPRS: Q18.1, U18.22
GRX: H2.3, R328.1
IO2: LED21.1, Q20.1, R318.2, U35.6
IO3: R316.1, U35.8
IO4: R315.1, U35.9
IO5: R314.1, U35.10
IO6: R313.1, U35.12
LINKA: Q14.1, U18.19
OUT1: CN1.6, Q19.10
OUT2: CN1.5, Q19.9
OUT3: CN1.4, Q19.8
OUT4: CN1.3, Q19.7
PPS: R345.1, U10.4
RE: R324.2, SW2.1, U18.26
RST: R325.1, SW1.2, U18.15
RX: H2.1, R308.1, U35.27
RX2: H3.2, U35.26
SIM_CLK: C52.2, CARD5.3, D5.4, U18.13
SIM_DATA: C51.2, CARD5.7, D5.1, R79.2, U18.11
SIM_RST: C53.2, CARD5.2, D5.5, U18.12
SIM_VCC: C54.2, C63.2, CARD5.1, CARD5.6, D5.3, R79.1, U18.14
TX: R309.1, U35.28
TX2: H4.1, U35.25
UEN: R337.2, R351.1, U35.14, U41.4
V38: R339.2, U41.5
VIN: C67.2, C70.2, D7.1, Q19.6, R57.2, R307.1, R332.1, U33.5, U34.1
WORK: Q13.1, U18.23
XL_N: C71.1, U35.29, X1.3
XL_P: C72.1, R310.2, X1.1
ZD: C91.2, R347.2, U35.13, U42.2
